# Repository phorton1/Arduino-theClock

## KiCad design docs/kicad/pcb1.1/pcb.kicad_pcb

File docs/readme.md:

# theClock - my first attempts at making a electromagnetic wooden geared clock

Please see [**theClock3**](https://github.com/phorton1/Arduino-theClock3)
for a more functional, and better documented electromagnetic wooden clock for **makers**.

This project is being documented *posthumously* in order to preserve the lineage of my clock oriented projects
so it **does contain all the fusion360 files, DXF files, and other results of the project** in case you are
interested.

## When and Why?

Around November of 2022, I had completed the [**20 mm CNC machine**](https://github.com/phorton1/Arduino-esp32_cnc20mm)
project and was using that machine to create various wooden boxes and other projects.  I was having fun with
the laser cutting capabilities of the machine and decided I wanted to try something with wooden gears in it.
After a few weeks of mulling the kinds of things I could build with wooden gears ... novelty boxes, or maybe
wooden robots, cars, etc ... I hit on the notion of making a **wooden clock**.

So I began obsessing about clocks in general and wooden clocks in particular.  One prolific online source
of information is [**Brian Law**](https://www.woodenclocks.co.uk/) and his many clocks, webpages and designs.
Although not wooden, I quickly found [**Steve Peterson's**](https://www.youtube.com/@stevesclocks)
series of 3D printed clocks interesting.  I explored dozens of existing designs, from the most artistic,
to the most rudimentary simple escapement mechanisms.

My diode laser cutter is limited to cutting about 1/4" (or less) wood.

As it turned out, I could not find a single existing design that I could make using
the tools and materials I had available to me.  My goal was to **laser cut** most of the pieces
from thin, cheap, available plywood and possibly 3D print a few other parts.   This is not
to dis any of the many great, and complete, and sometimes free designs out there.  But, I
actually live in an apartment, don't have access to a table saw or similar typical woodworking
tools.  Most of the designs for clocks that I found online involved thicker woods, typically hardwoods,
and the use of the usual woodworking tools.

Although you can find a number of *clock
making kits* that use laser cut plywood **for sale** online, I could not find any free
online designs for such clocks.  Finally, with regards to the existing laser pre-cut
kits that *are* available, even for pay, none of them captured what I was trying to achieve.
Although beautiful and complex, the available *kits* are more or less uniformly intended as
snap-together novelty clocks and not really designed to be permanently constructed and
act as actual time pieces.

So, I determined I would just learn what was necessary and design my clock from scratch.

Probably the first requirement that I arrived at was that I wanted the clock to be
electromagnetically driven. The real study and discipline of
[**Horology**](https://en.wikipedia.org/wiki/History_of_timekeeping_devices),
and clocks as we know them, centrally involves the evolution of
[**gravity escapement mechanisms**](https://en.wikipedia.org/wiki/Escapement#Deadbeat_escapement).
But I did not want to build a clock that had to be rewound (or it's weight lifted) every day or week.
I wanted something I could put on a shelf, and forget, and that would keep time fairly
reliably ... that is that it would function as an actual clock in my living space.

So I elected early to have an electromagnetically driven pendulum, while maintaining
the idea that it would have wooden, laser cut gears.

I thought it would be *so much easier* than it turned out to be!  In fact, my original
notion was to build a **chaotic clock** that, despite being chaotic, still kept accurate time, an idea I
may yet revisit.  The idea was to build a dual pendulum clock that could be intentionally
driven into a chaotic motion, but that could be recovered to periodicity at
small amplitudes, and then to have the clock randomly intersperse chaotic movements
of the pendulum with regular time-keeping movements to correct and adjust for
the chaos.  It was to be called **The Perception of Time**, alluding to the fact
that humans just do not experience time in a linear manner. Also, in my dreams,
it would be artistic and/or have crazy gear trains like squares, triangles, or helices.

In any case, that remains a project for the possible future as I decided that,
since I only wanted to spend a few weeks on the project, I had just better build
a simple clock.

**I had a lot to learn**

## A Few Requirements

As with all of my projects, I started off by listing a few requirements for the project.

- It would largely be made of **thin laser cut plywood** (as described above)
- It would use an **electromagnetically driven pendulum**
- It would have concentric **hour**, **minute**, and **second hands**
- It would keep **reasonably accurate** time, the definition of which was yet to be determined.
- It would **not** look like, or be constructed like a **snap together kit**.
- It would look like a **permanent construction** .. a *real clock*, yet ....
- It would be built in such a way that it could be **disassembled** and **repaired** or **modified** if necessary
- It would make use of an **MPU** (Microprocessor) like an Arduino or an ESP32
- It would have a custom made **PCB** (Printed Circuit Board)
- The PCB and electromagnetic coils would be hidden, unobtrusively powering the clock
- The **magnet** on the pendulum would **pass between two coils** rather than *over one coil* (discussed below)

The requirement about being able to be **disassembled** and and **repaired** or **modified** warrants
a brief discussion.

Especially since I had no idea if the clock would even work, or what refinements might be needed,
I decided to design the clock in such a way that, as much as practicable, I would be able to disassemble
and re-assemble it multiple times in case I needed to modify the mechanical aspects of the clock
along the way.   Also, not having any idea about the lifespan of
such a clock, it was important to me to be able to, at some point in the future, disassemble and
repair and/or rebuild the clock in case the gears or parts of the wooden mechanism
*wear out*.

Given a general idea of the requirements of the project, I then proceeded into a **research
phase** to learn as much as possible about these kinds of clocks before constructing one.
I downloaded and analyzed virtually any clock design that I could find, even if they did not
match my construction criteria, just to get an idea of how other people had approached
building wooden (or any) clocks.  This included a number of complete **Fusion 360** designs,
but also a number of available (free) online **books** about the subject.

## Electromagnetism and Gravity

It was a wonderful journey!   I spent days, and sometimes all night, reading histories
and perspectives of clock making, which turn out to be pretty fundamental to science,
and the development of civilization as we know it.  The **research phase** broadened
out into a review, as it were, of pretty much **the entire history of science** lol.

It led me to re-touch my basic understandings of **physics** and **mathematics**,
going back through **Newton** and *Calculus 101*, but really took me on a journey
through most of human history.   From sun dials, to the Aztecs and their calendars,
Pythagoras and the Greeks, I was all over the place reading about the history of how humans
came up with the notion of time ... and measuring it.

Galileo famously notices the period of a [**pendulum**](https://en.wikipedia.org/wiki/Pendulum)
is nearly independent of it's amplitude ... that is that a pendulum swings at about
the same rate regardless of how wide it swings.
[Christiaan Huygens](https://en.wikipedia.org/wiki/Christiaan_Huygens) creates
a gravity escapement mechanism to produce the world's most accurate clock
of the 1600's ... accurate to a few minutes a day.

One of my favorite reads was learning more about
[Robert Hooke](https://en.wikipedia.org/wiki/Robert_Hooke), the
creation of the [Royal Society](https://en.wikipedia.org/wiki/Royal_Society),
and Hooke's rivalry with Issac Newton.  **Did you know that Robert
Hook was the first human to ever create a tone of a known frequency?**
LOL, he created a gear mechanism with a paper card, and by knowing
the gear ratios and counting off the seconds with a clock, he could
ascertain the frequency of the resulting tone.

It was approximately a G# lol, on his piano, in case you're wondering,
although the **tuning fork** would not be invented for another 150 years,
and the semi world-wide standardardization to A440 tuning until the
middle 1900's - after WW1.

In any case, or rather, of course, that led me through the whole
[Age of Enlightment](https://en.wikipedia.org/wiki/Age_of_Enlightenment)
before I could relish re-learning about the greats in the discovery
and understanding of [Electromagnetism](https://en.wikipedia.org/wiki/Electromagnetism).
Volta!  Gauss!  Ampere!  Lorenz!  Michael effing Faraday!

**And then came [Maxwell](https://en.wikipedia.org/wiki/James_Clerk_Maxwell)**

All of sudden we're talking about **the speed of light** !!!

Another fun fact: **Did you know that [Michelson](https://en.wikipedia.org/wiki/Albert_A._Michelson)
and [Morely](https://en.wikipedia.org/wiki/Edward_W._Morley) used a *pendulum* in their
groundbreaking attempts to measure the speed of light?** Yup.  They used one to determine
the local gravity in Pasadena, CA, which was part of their calculations of the speed of
light.

In any case, all of this stuff was very interesting, and I got to re-learn
a lot, and learn a lot of new stuff as I started designing silly wooden clocks!

## Experiments - Pendulum Prototypes

I thought it would be a good idea to just build a pendulum and see if I
could get it to swing with an electromagnet.   I 3D printed a little
white pendulum that was about 5 inches high and using some coils removed
from a couple of of micro-solenoids I had laying around. I
created a circuit with an Arduino and a motor controller module
to send pulses of electricity to the coils.

That worked in a few hours.  The pendulum had a magnet in it, and
could be made to swing back and forth (fairly rapidly).

Then I designed and built a bigger pendulum, learning in the process that
I'm not so bright!   LOL.

I thought I would make a [**linear motor**](https://en.wikipedia.org/wiki/Linear_motor)
(I was still clinging to the *chaotic pendulum* idea),
so that I could swing the pendulum really fast, or really slow,
or even stop it in the middle of a swing.   Since magnets
are cheap, and coils are expensive (and fairly hard to make), and since
most linear motors **move the coil** through stationary magnetic fields,
that was my initial stab.

I designed the Pendulum in Fusion 360.  I salvaged the magnet wire
from the transformer of an old wall wart and hand wound the coils.  I laser cut
the pendulum from wood and 3D printed the plastic framework to go on some
2020 aluminum extrusions.
I put **two coils** on the pendulum and had it swing through the fields of a
series of magnets, and extended the bread boarded **Arduino** control circuit,
thinking I could then simply control it's position
in real time as one would with a linear motor.

**Nope**.

I got it moving, but it turns out that (a) the pendulum wants to swing at a particular rate;
it did not want to move at arbitrary frequencies,
(b) you basically don't want a bunch of wires and junk on the pendulum,
as that decreases it's accuracy, and, perhaps more importantly,
in my configuration (c) the electromagnetic coils were not nearly strong
enough to stop and hold the pendulum at any given point, (d) this linear
motor was at best, like a stepper motor, and the motion was jerky and
not smooth.

Before moving on, I removed the magnets, one at a time, in a series of experiments,
until I ended up with a single magnet and the two coils on the pendulum that
I could sort of control.  At that point, though I could get the pendulum to swing
fairly reliably, I could not really control it's period.

Another thing I *did* experiment with here was using the Arduino to not only
**pulse the electromagnet** to attract or repulse the magnets
and move the pendulum, but was also to **use the coil as a
sensing device**.   Since a coil moving through a magnetic field
creates a current, I could measure that current with the
computer and tell, for example, when the coil passed a magnet.

Most single coil electromagnetic clocks use that current sensing
capability (and a simple circuit) to detect a zero crossing for
the timing for delivering the repulsive impulse to keep the pendulum
moving.

After a few days I decided to just go ahead and start designing the
gears and things for a wooden clock.

## First (Bad) Design

Designing the gears and mechanics in Fusion 360 was not difficult, but
was time consuming.

Somehow I landed on the notion that my clock would have
four coils (two about the center of the swing and two at
the extremes) -- which are really eight coils since, in
my design, the magnet moves **between** the coils.

*Another side note:  I could find absolutely **no scientific studies**
or analyses about the effect of a magnet moving **between** two coils.
There were plenty of scholarly articles on solenoids, coils,
magnets moving near a coil, etc, but nowhere could I find an analysis
of the math involved when a magnet passes **between** two coils.*

I wanted my magnet to pass **between** two coils, rather than **over**
a single coil, as most magnetic clocks do, because I felt that the
**vector of force** from a coil underneath a magnet would tend
to make the pendulum **bump** as the impulse is applied.  The
force would not be **orthogonal** to the pendulum's axis of rotation.
By having the magnet move between the two coils, the majority of
the force would be put into moving the pendulum along it's line
of travel, rather than *up* or *down* (assuming the pulse is
applied shortly after the *zero crossing*) and that seemed
**more efficient** to me.

I was also *not thrilled* with the technique of **using the
coils as sensors**.   I did experiment with it extensively,
and it works, but it is onerous in the circuit and code to change the
Arduino's pins from **input** to **output** to be able sense milliamp
currents one millisecond, and then deliver 1/2 amp or more to the same coil
a few milliseconds later and the results were not that great.

Because I knew I would want to **know where the pendulum was** in it's
swing (particularly zero crossing), and I did not like the *coil sensing*
approach, in this initial design, because I had a few on hand,
I also added [**five hall sensors**](https://en.wikipedia.org/wiki/Hall_effect_sensor),
which are electrical components that can tell when a magnet is near
them, bracketting the four (pairs) coils with the idea that
I could use the information, particularly the zero crossing, but
also the extent of the swings, in controlling the clock..

Mind you, I still don't have any idea if, or how this thing is gonna work.

But in building the test rig above, I finally determined that I needed **some kind
of an actual full clock** to even test these concepts.  The **friction**
from the gears and the work that needs to be done, the **ratchet** mechanism,
the **length and weight of the pendulum**, all play a role in how fast
the clock ticks and how much force is needed to move the pendulum.

So I just designed and built a damned clock lol, pressing through the
design even if I was not sure about if, or how, it would work.

An actual full implementation allowed me to test the simple mechanics,
gears, gear ratios, the ratchet mechanism, and so on, all of which worked
**pretty good**, more or less, on the fist build, right out of the
design gate, as it were.

I also made a [**coil winding machine**](https://github.com/phorton1/Arduino-CoilWindingMachine), as hand winding
these coils is really tedious and inexact, and I had to
make eight of them!!

I started off using an **Arduino** on a breadboard as the computer, but
quickly decided that I would rather have a more powerful and sophisticated **ESP32**, not
only because it's speed would allow me a lot more flexibility in the
implementation, but also because the ESP32 **includes WiFi and a built in RTC**
(real time clock), whereas the Arduino doesn't.  The RTC
would come into play to keep the clock accurate, and with the WiFi I would
be able to access **NTP** (Network Time Protocol) as well as provide a **WebUI** for
remote **control, monitoring, and debugging** of the clock.

So I also designed a circuit for an ESP32 and built the first custom PCB
for the clock.  With 4 (pairs of) coils, sigh, I used **two L293D** H-bridge
motor drivers so that I could control each (pair of) coils to either
repulse or attract the pendulum magnet under MPU control.

I got it going ... it ticked and tocked .. and the second
hand moved, but the clock was not even close to keeping good time

I called this version 1.0.

## Simplifying and Getting it working (sort of)

Without going into too much gruesome detail, I quickly learned that
having so many coils was a headache and did not really help me to
control the pendulum and it's timing.  What I needed was a single,
bigger, and more powerful coil, so I retrofitted the clock with
a single bigger coil.

I also ended up *embedding the coils in epoxy* so that I could eliminate
the plastic (on the *bobbin*) between the coil and the magnet to
reduce the distance and increase the force.  Even 1mm of distance
less increased the force applied to the pendulum significantly.

### Adding the magnetic spring

As I said, I thought it would be easier.  With my 4 coil design I had
been planning to control the frequency of the pendulum by using the
outer pair of coils to either attract, or more likely repulse, the
pendulum on each swing so that I could speed it up or slow it down.

That also proved difficult to impossible, in practice, for me to accomplish.

I hit on the idea of controlling the frequency **BY** controlling
the amplitude at about that time.    **If I just had a spring ...**

hmmm ... what if I just have **one coil** and put a set of permanent
magnets near the extreme of the swing that repulse the magnet in the pendulum?
Then wouldn't it be the case that on wide swings the pendulum would **bounce**
off those springs, making it go faster?   And then couldn't I reduce the
amplitude of the pendulum (by putting less energy into it) so that it would
not bounce off the springs, and would then tick slower as a result of that?

So I retrofitted the clock with these **magnetic spring** thingees,
switched to a single coil, rewrote most of the software, and within
a week or so of the first build, I had achieved a clock
that could sort of keep time.

I called this **version 1.1**.

## Version 2

I spent a lot of time messing around version 1.1, particularly
mucking around with the code.

It was not pretty.  There is a PID controller
that adjusted the energy put into each swing based on the
milliseconds error, but I also needed to add a few "heuristics" (**kludges**)
to keep the clock running reasonably ... to prevent it
from "stalling" while trying to slow down, or banging back and
forth while trying to speed up.

After a week of effort, Version 1.1 was probably accurate to a few minutes a day.

Since I wanted to make a clock as a gift to someone for Christmas, and I was
running out of time, I did one more quick design pass to rectify the worst
problems with Clock1 and pressed on with another build:

- the wooden frame was not square and the clock did not sit flat,
  so I designed a 3D printed base which at least kept the clock
  itself from rocking back and forth
- I formalized the design of the magnetic springs so that they
  could be more accurately adjusted.
- I designed and built a **new PCB** that only used one LM293D
  motor controller
- I added a **face** with numbers to the clock.

I laser cut a whole new clock, and all the parts, 3d printed stuff,
made the new circuit board, soldered it up, wound coils, sanded all the gears (pain!),
painted everything, and so on, put it together, and, after putting
it through a quick testing cycle, I sent it away.

I would say that it was accurate to a few minutes a day at it's best.

I did not even get a chance to test it for a week before gifting it :-(

Nor had I, in the code, gotten around to any notion of utilizing
the ESP32's RTC (real time clock), much less using NTP (Network
Time Protocol) to make the clock accurate over any time scales
(though I had laid the groundwork in the code, WebUI, etc)

It just tried to beat at 1000ms per swing.

I called this "theClock - Version 2"

## Design problems with Versions 1 & 2

Part of it was the mechanics .. it was missing beats or sometimes
grabbing two gears.  There were friction problems, and, I think,
misalignment causing the gears to bind at times. But also
part of it was the software and heuristics, which
were hamstrung with the *information* available to the software in
order to control the pendulum, and somewhat hastily written
and not really that well tested.

From these initial clocks I came up with the following list of **problems**:

- The use of **dowels** to connect the different **planes** of the clock did not work well.   If the dowels
  were fitted into thick pieces of hardwood, and the holes were drilled square, then the dowels could
  facilitate a **square frame**.  However, because the holes are merely in thin pieces of plywood,
  the dowels were not inherently square to the frame.  In other words, there were alignment issues
  between the *planes* of the clock, which caused **a lot of friction** and **binding of the clock**
  as the hands and gears turned.    This was particularly true when taken with the requirement that the
  clock be **disassemble-able** and the clock was only **screwed** together in the final assembly.
  To get it to work, I had to *dry build** the clock, twist the dowels and position the planes
  the best I could, **apply epoxy glue**, and then literally hold it together with my hands as the glue set
  in order to achieve any degree of alignment.
- The **ratchet mechanism** requires the pendulum to do **all of it's work** while swinging in one
  direction, and does **no work** while swinging in the other direction.  This made the pendulum
  swing (and forces involved) **lopsided** and caused an uneven beating of the clock. It would
  swing much more, and more easily, to one side than to the other.
- More importantly, the **ratchet mechanism** is directly coupled the pendulum to the pawls, so
  that **the wider the pendulum swings, the further the second hand moves**!!  This resulted
  in the mechanism being unreliable, particularly to the degree that I was trying to control
  the **frequency** of the pendulum by increasing or decreasing the **amplitude** of the swing.
  I found that, at wide swings, the pawl would sometimes **grab two teeth** and advance the clock
  **two seconds** at a time, or arguably worse, in smaller swings it would sometimes **fail to move
  the seconds hand at all** (a condition I called a **stall**).
- The five **Hall Sensors** did not provide me with enough **resolution** about the position
  of the pendulum to implement a good **PID Controller** (algorithm for controlling the clock),
  and as a result, the swing would vary wildly while trying to speed up or slow down the clock,
  sometimes banging the left and right limits of travel (and grabbing two teeth!) or other times
  failing to even grab a tooth and move the seconds hand (stalling).
- Due to time constraints I had not been able to implement any code that took advantage
  of the ESP32 **RTC** (Real Time Clock) or the available **NTP** (Network Time Protocol) to
  make the clock more accurate.

Although I compensated for the resolution problem by putting heuristics into the code for these cases,
in subsequent clocks I utilized a different, more accurate way of sensing the position of the pendulum
which led to a much simpler algorithm, and smoother and more precise control of the
pendulum, in turn resulting in a much more pleasing and consistent swing.

### Postscript

After I built [**theClock3**](https://github.com/phorton1/Arduino-theClock3), I felt bad
for my old forlorn clock version 1 sitting there on the shelf, so I retrofitted it with
the **AS5600 angle sensor** and **software** from *theClock3* resulting in it *keeping
much better time* and having a *much nicer swing* (even though it is not as accurate,
or trouble free as *theClock3*) ..

### **Next:** After versions 1 & 2, I designed and implemented [**theClock3**](https://github.com/phorton1/Arduino-theClock3)

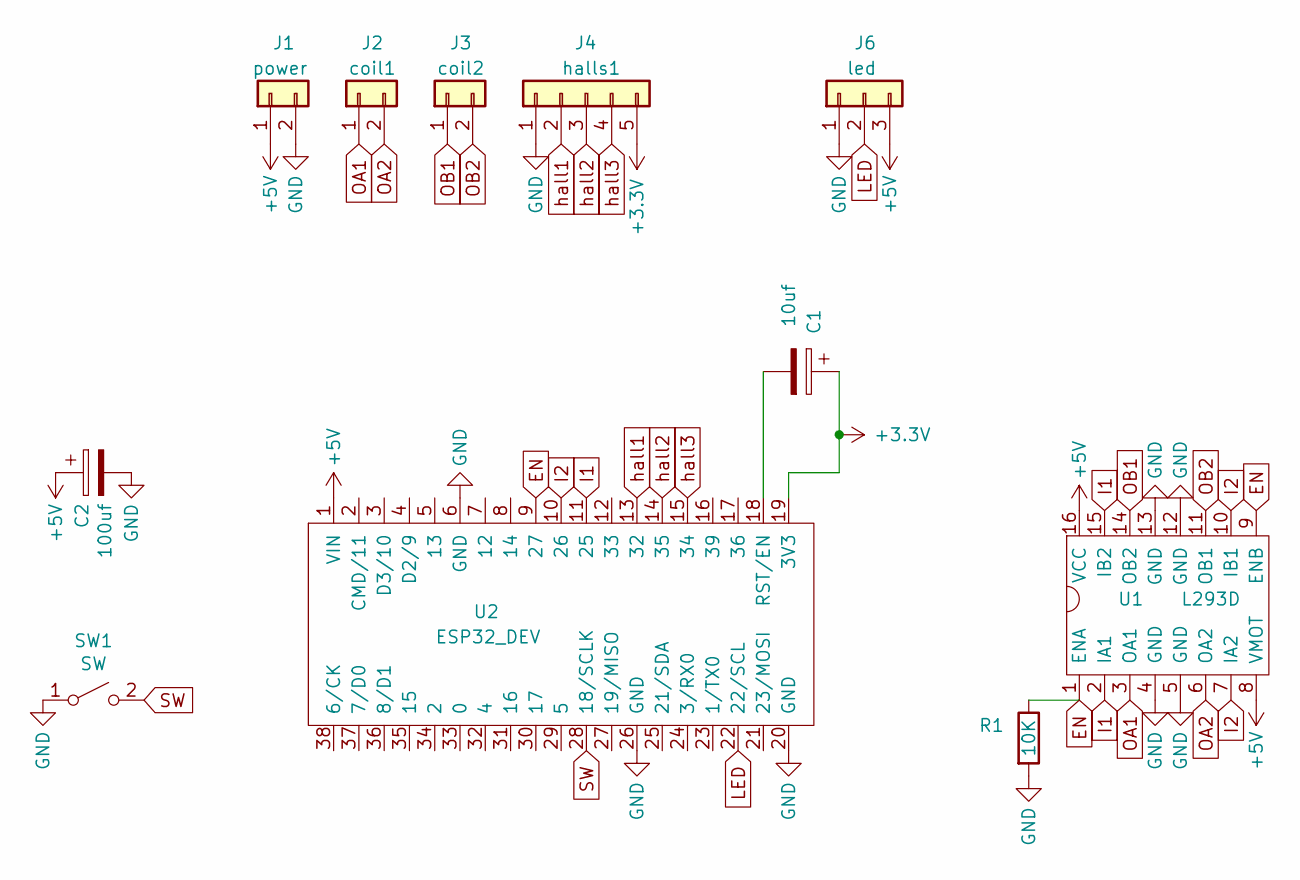
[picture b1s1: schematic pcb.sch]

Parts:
C1: 10uf; my2pin
C2: 100uf; my2pin
J1: power; my2pin
J2: coil1; my2pin
J3: coil2; my2pin
J4: halls1; my5Pin
J6: led; my3pin
R1: 10K; myResistor
SW1: SW; right_angle_button
U1: L293D; myDip16
U2: ESP32_DEV; ESP32-DEV

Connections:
+3V3: C1.1, J4.5, U2.19 (3V3)
+5V: C2.1, J1.1, J6.3, U1.8 (VMOT), U1.16 (VCC), U2.1 (VIN)
EN: R1.1, U1.1 (ENA), U1.9 (ENB), U2.9 (27)
GND: C2.2, J1.2, J4.1, J6.1, R1.2, SW1.1 (A), U1.4 (GND), U1.5 (GND), U1.12 (GND), U1.13 (GND), U2.6 (GND), U2.20 (GND), U2.26 (GND)
I1: U1.2 (IA1), U1.15 (IB2), U2.11 (25)
I2: U1.7 (IA2), U1.10 (IB1), U2.10 (26)
LED: J6.2, U2.22 (22/SCL)
unnamed: C1.2, U2.18 (RST/EN)
OA1: J2.1, U1.3 (OA1)
OA2: J2.2, U1.6 (OA2)
OB1: J3.1, U1.14 (OB2)
OB2: J3.2, U1.11 (OB1)
SW: SW1.2 (B), U2.28 (18/SCLK)
hall1: J4.2, U2.13 (32)
hall2: J4.3, U2.14 (35)
hall3: J4.4, U2.15 (34)

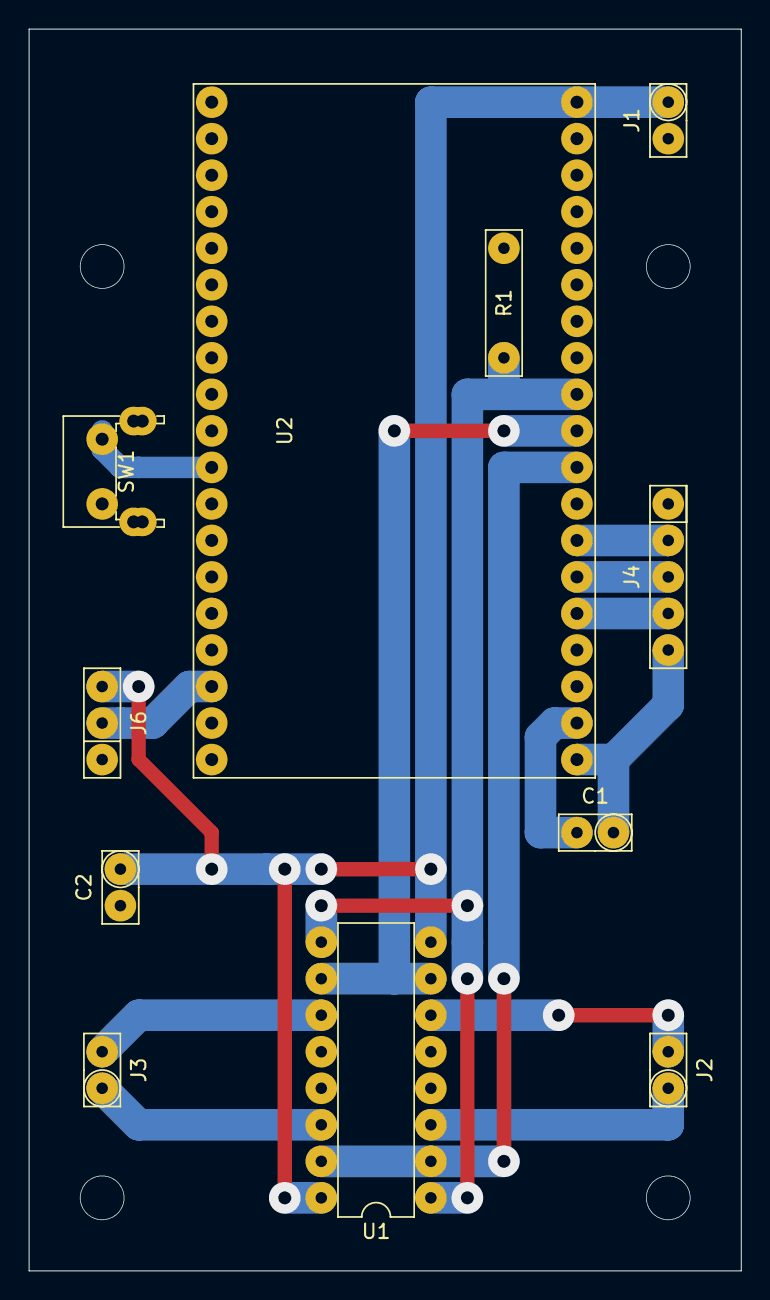
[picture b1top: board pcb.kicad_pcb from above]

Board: 2 copper layers, 49.5 x 86.4 mm, 11 parts (0 on the bottom side), 16 nets.

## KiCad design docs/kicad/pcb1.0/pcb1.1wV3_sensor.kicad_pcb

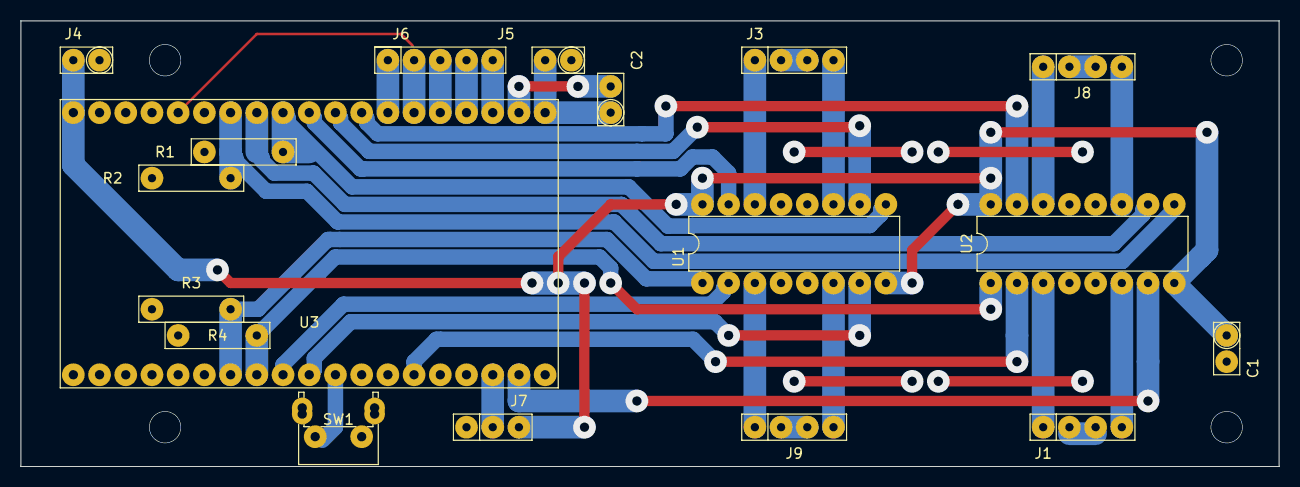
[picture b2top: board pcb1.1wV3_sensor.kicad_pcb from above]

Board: 2 copper layers, 121.9 x 43.2 mm, 18 parts (0 on the bottom side), 35 nets.

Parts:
C1: 100uf; my2pin
C2: 10uf; my2pin
J1: coil48; my4pin
J3: coil15; my4pin
J4: power; my2pin
J5: hall_power; my2pin
J6: halls; my5Pin
J7: led; my3pin
J8: coil126; my4pin
J9: coil37; my4pin
R1, R2, R3, R4: 10K; myResistor
SW1: SW; right_angle_button
U1, U2: L293D; myDip16
U3: ESP32_DEV; ESP32-DEV

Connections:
+3V3: C2.1, J5.2, U3.19
+5V: C1.1, J4.2, J7.3, U1.8, U1.16, U2.8, U2.16, U3.1
ENA: R1.1, U1.9, U3.9
ENB: R2.1, U2.9, U3.7
ENC: R3.1, U1.1, U3.32
END: R4.1, U2.1, U3.31
GND: C1.2, J4.1, J5.1, J7.1, R1.2, R2.2, R3.2, R4.2, SW1.1, U1.4, U1.5, U1.12, U1.13, U2.4, U2.5, U2.12, U2.13, U3.6, U3.20, U3.26
IA1: U1.10, U3.11
IA2: U1.15, U3.10
IB1: U2.10, U3.8
IB2: U2.15, U3.12
IC1: U1.2, U3.30
IC2: U1.7, U3.29
ID1: U2.2, U3.25
ID2: U2.7, U3.21
LED: J7.2, U3.22
unnamed: C2.2, U3.18
unnamed: J1.2, J1.3
unnamed: J3.2, J3.3
unnamed: J8.2, J8.3
unnamed: J9.2, J9.3
OA1: J3.4, U1.11
OA2: J3.1, U1.14
OB1: J8.4, U2.11
OB2: J8.1, U2.14
OC1: J9.1, U1.3
OC2: J9.4, U1.6
OD1: J1.1, U2.3
OD2: J1.4, U2.6
SW: SW1.2, U3.28
hall1: J6.1, U3.13
hall2: J6.2, U3.14
hall3: J6.3, U3.15
hall4: J6.4, U3.16
hall5: J6.5, U3.17

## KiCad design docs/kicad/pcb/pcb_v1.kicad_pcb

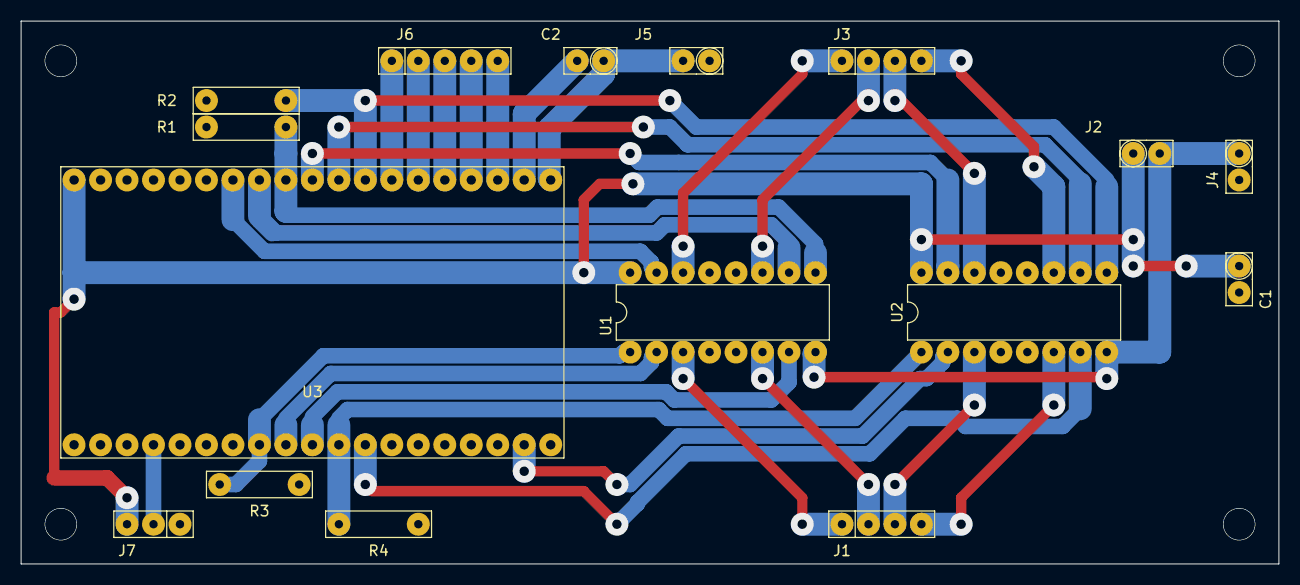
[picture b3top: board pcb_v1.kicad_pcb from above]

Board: 2 copper layers, 120.7 x 52.1 mm, 16 parts (0 on the bottom side), 31 nets.

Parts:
C1: 100uf; my2pin
C2: 10uf; my2pin
J1: coil34; my4pin
J2: jumper; my2pin
J3: coil12; my4pin
J4: power; my2pin
J5: hall_power; my2pin
J6: halls; my5Pin
J7: led; my3pin
R1, R2, R3, R4: 10K; myResistor
U1, U2: L293D; myDip16
U3: ESP32_DEV; ESP32-DEV

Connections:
+3V3: C2.1, J5.2, U3.19
+5V: C1.1, J2.1, J7.3, U1.16, U2.16, U3.1
ENA: R1.1, U1.9, U3.9
ENB: R2.1, U2.9, U3.12
ENC: R3.1, U1.1, U3.31
END: R4.1, U2.1, U3.28
GND: C1.2, J4.2, J5.1, J7.1, R1.2, R2.2, R3.2, R4.2, U1.4, U1.5, U1.12, U1.13, U2.4, U2.5, U2.12, U2.13, U3.6, U3.20, U3.26
IA1: U1.10, U3.8
IA2: U1.15, U3.7
IB1: U2.10, U3.11
IB2: U2.15, U3.10
IC1: U1.2, U3.30
IC2: U1.7, U3.29
ID1: U2.2, U3.21
ID2: U2.7, U3.27
LED: J7.2, U3.35
unnamed: C2.2, U3.18
OA1: J3.2, U1.11
OA2: J3.1, U1.14
OB1: J3.4, U2.11
OB2: J3.3, U2.14
OC1: J1.1, U1.3
OC2: J1.2, U1.6
OD1: J1.3, U2.3
OD2: J1.4, U2.6
VSS: J2.2, J4.1, U1.8, U2.8
hall1: J6.1, U3.13
hall2: J6.2, U3.14
hall3: J6.3, U3.15
hall4: J6.4, U3.16
hall5: J6.5, U3.17

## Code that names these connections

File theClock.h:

#pragma once

#include <Arduino.h>
#include <myIOTDevice.h>

#define COMPILE_VERSION  2
	// sets the (old) static HALL calibration values for V1 vs V2
	// and the myIOT device name and version

#define PIN_HALL1	32
#define PIN_HALL2	35
#define PIN_HALL3	34

// Note that ENB, INB1, and INB2 are sent out for backward
// compatability for V1 circuit board but unused on V2

#define PIN_ENA		27
#define PIN_INA1	25
#define PIN_INA2	26
#define PIN_ENB		4
#define PIN_INB1	17
#define PIN_INB2	5

#define PIN_LEDS	22
#define PIN_BUTTON  18

#define PIXEL_MAIN		0
#define NUM_PIXELS		1

#define MY_LED_BLACK    0x000000
#define MY_LED_RED      0x440000
#define MY_LED_GREEN    0x003300
#define MY_LED_BLUE     0x000044
#define MY_LED_CYAN     0x003333
#define MY_LED_YELLOW   0x333300
#define MY_LED_MAGENTA  0x330033

#define MY_LED_WHITE    0x444444

#define MY_LED_ORANGE   0x402200
#define MY_LED_REDMAG   0x400022
#define MY_LED_BLUECYAN 0x002240


//------------------------
// theClock definition
//------------------------

#define ID_RUNNING			"RUNNING"
#define ID_PID_MODE			"PID_MODE"
#define ID_PLOT_VALUES		"PLOT_VALUES"

#define ID_HALL_THRESH		"HALL_THRESH"

#define ID_POWER_LOW      	"POWER_LOW"
#define ID_POWER_HIGH      	"POWER_HIGH"
#define ID_POWER_MAX      	"POWER_MAX"
#define ID_POWER_START      "POWER_START"

#define ID_DUR_LEFT      	"DUR_LEFT"
#define ID_DUR_RIGHT      	"DUR_RIGHT"
#define ID_DUR_START		"DUR_START"

#define ID_PID_P			"PID_P"
#define ID_PID_I			"PID_I"
#define ID_PID_D			"PID_D"

#define ID_CLEAR_STATS		"CLEAR_STATS"

#define ID_CUR_TIME			"CUR_TIME"
#define ID_TIME_LAST_START  "LAST_START"
#define ID_STAT_RUNTIME		"TIME_RUNNING"
#define ID_STAT_BEATS		"BEATS"
#define ID_STAT_RESTARTS	"RESTARTS"
#define ID_STAT_STALLS_L	"STALLS_LEFT"
#define ID_STAT_STALLS_R	"STALLS_RIGHT"
#define ID_STAT_ERROR_L		"ERROR_LOW"
#define ID_STAT_ERROR_H		"ERROR_HIGH"
#define ID_STAT_DUR_L		"DUR_LOW"
#define ID_STAT_DUR_H		"DUR_HIGH"
#define ID_MIN_POWER_USED	"MIN_POWER_USED"
#define ID_MAX_POWER_USED	"MAX_POWER_USED"

#define ID_STAT_INTERVAL	"STAT_INTERVAL"



class theClock : public myIOTDevice
{
public:

    theClock();
    ~theClock() {}

    virtual void setup() override;
	virtual void loop() override;

private:

    static const valDescriptor m_clock_values[];

	static bool _clock_running;
	static bool _pid_mode;
	static uint32_t _plot_values;

	static int _hall_thresh;

	static int _power_low;		// STATIC: power when sensor reached; PID: mininum power
	static int _power_high;		// STATIC: power when sensor not reached;  PID: starting power
	static int _power_max;      // PID: maximum power
	static int _power_start;    // power during startup pulse

	static int _dur_left;		// duration of left power pulse for both PID and STATIC
	static int _dur_right;		// duration of right power pulse for both PID and STATIC
	static int _dur_start;		// duration of startup pulse

	static float _pid_P;
	static float _pid_I;
	static float _pid_D;

    static uint32_t _time_last_start;
	static uint32_t _cur_time;
	static String _stat_time_running;
	static uint32_t _stat_beats;
	static uint32_t _stat_restarts;
	static uint32_t _stat_stalls_left;
	static uint32_t _stat_stalls_right;
	static int _stat_error_low;
	static int _stat_error_high;
	static int _stat_dur_low;
	static int _stat_dur_high;
	static uint32_t _min_power_used;
	static uint32_t _max_power_used;

	static uint32_t _stat_interval;

	static void startClock();
	static void stopClock();
	static void clearStats();

    static void onClockRunningChanged(const myIOTValue *desc, bool val);
    static void onPIDModeChanged(const myIOTValue *desc, bool val);

	static void run();
	static void clockTask(void *param);
};


extern theClock *the_clock;

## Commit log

2022-11-27 added design.md (to test github directory structure)
2022-11-30 prep for V2 (single coil) circuit board by duplicating and moving kicad stuff into separate folders
2022-12-02 updated to V1.1 - single coil and 3 hall sensors
2022-12-11 renamed pcb 2.0 to 1.1 - WIP
2022-12-11 moved pcb1.1 mounting hole
2022-12-14 finished pcb
2022-12-18 CLOCK 2.0 - initial changes: version number, hall calibrations
2022-12-19 sanity checking before new algorithm
2022-12-20 MAJOR REV to V2 - Change to single right pulse algorithm, get rid of "over positions" add WIFI on/off (default==off) via base/bat/platform_setup.pm, cleanup all defines, etc, etc, etc
2022-12-20 implemented button control and led pixel feedback
2022-12-20 uploaded new software to old clock V1
2022-12-27 added dur_left to cope with my weak v1.1 clock; tuned
2022-12-29 Tuning old v1 clock
2023-01-04 added STAT_DURATION to configuration
2023-01-22 COMMENTS - brought comments up to date with my V1.0 running fairly well
2023-02-18 added some NTP test code
2023-04-19 diagram v1.3 (v1.1 plus v3 sensor & software)
2023-06-07 updated to new captive.html (Source Code is now Obsolete but will be retained to show pics of old clocks)
2023-06-12 initial commit of documentation WIP
2023-06-12 test commit and push
2023-06-13 upload initial PUBLIC version
2023-06-13 remove obsolete statement ... it is what it is
2023-06-13 readme typos
2023-06-16 added link to new Arduino-CoilWindingMachine repository
2023-10-10 added LICENSE.TXT and empty docs/readme.md to most public repositories
2023-10-20 updated to myIOT changes from a while ago - ID_DEVICE_WIFI changed to ID_WIFI - VALUE_STORE_MQTT_SUB - changed to VALUE_STORE_SUB
2024-02-20 normalize myIOT data directories against Arduino/Libraries myIOT/data master
2024-03-01 get rid of /data folder in prep for submodule
2024-03-01 made 'data' directory into submodule of myIOT/data_master
2024-07-18 submodule(data) auto_commit(3ef3db13) iotCommon.js - added app disable control functionality
2024-07-19 submodule(data) auto_commit(9478759f) addl iotCommon.js submodule changes for control and disabled_classses
2024-09-21 submodule(data) auto_commit(83767cf1) Added a Widget tab to the main myIOT webpage; added jqplot CSS and JS files; wrote iotPlot.js prototype of charting within a "widget" - see fridgeController chec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
2024-09-22 submodule(data) auto_commit(0465efe4) myIOT Widets II - introduce basic HTTP caching; refactor myIOT iotPlot.js into iotCommon.js, cleanup Widget concepts and code; sanity checkcin
2024-09-22 submodule(data) auto_commit(e76456cf) iotPlot.js - minor change to Fix Zooming; otherwise "comments only"
2024-09-24 submodule(data) auto_commit(86b02898) created a WS based Plotter!
2024-09-25 submodule(data) auto_commit(331f60b7) refined myIOT plotter with LEGENDS and using device specific PLOT_TYPES if available; theClock3 implementation of PLOT_CYCLES and PLOT_WAVES
2024-09-25 submodule(data) auto_commit(18ec6f60) iotPlot.js - missing ctx.lineWidth = 1; for plot itself
2024-09-26 submodule(data) auto_commit(68039dc2) prep for bilgeAlarm bar chart widget - reworked myIOTDataLog to send records from back of file until dt stamp is met, which required myIOTWebServer to use HTTP 1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
2024-09-29 submodule(data) auto_commit(416ed000) added prototype bilgeAlarm jqPlot Widget using added "alt_data_format" and custom chart_header and chart_data code in onCustomLink(). modified myIOT/data index.h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
2024-10-01 submodule(data) auto_commit(2407a228) added global DEGREE_TYPE and VALUE_STYLE_TEMPERATURE, supprted in webUI, dataLog, and Charts
2024-10-06 submodule(data) auto_commit(28556b88) iotCommon.js - changed keep_alive timings and const's to vars to allow debugging at runtime
2024-10-07 submodule(data) auto_commit(f3e2065d) reduce size of WS status fields in index.html
2024-10-10 submodule(data) auto_commit(b622c3ba) Use regular javascript alert instead of myAlert and hide progress on upload_error
2024-10-19 submodule(data) auto_commit(c0e7ba5a) add better resizing to iotChart.js
2024-10-21 submodule(data) auto_commit(b811e3f8) move generic uiButtons to myIOTButtons; implement initial tempController uiScreen and PCB board(s)
2024-10-25 submodule(data) auto_commit(fdbad871) fix myIOTServer with new chart stuff (pass uuids, caching, etc)
2025-12-15 submodule(data) auto_commit(b649fc3a) iotChart.js - added scheme for setting device specific series colors
2025-12-18 submodule(data) auto_commit(1adaeb45) reworked iotChart.js incremental update scheme starting with Arduino-boat-drainPump
2025-12-18 submodule(data) auto_commit(b6ac0c88) starting in Arduino-boat-arirco, major rework of iotChart.js and how charts are implemented - use common chart.html instead of specific/extra_data/device_chart.h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
2025-12-18 submodule(data) auto_commit(1efc7b72) rework iotChart.js::determineNumberTicks() starting with drain_pump
2025-12-18 submodule(data) auto_commit(78894e93) change onChartResize() to use create_chart() instead of built in jqplot.replot()
2025-12-18 submodule(data) auto_commit(40916b0c) separate iotChart.js doChart() as init only method from onXXX() UI methods - yet another rework of iotChart.js and myIOTDataLog starting with fridgeController
2025-12-18 submodule(data) auto_commit(b923e44d) back to static html for chart.html; got rid of myIOTDataLog::getChartHtml() starting with tempController
2025-12-18 submodule(data) auto_commit(a4e2ed81) change chart.html and iotChart.js to use and remove style "degree_hidden" for devices that chart things with degrees
2025-12-18 submodule(data) auto_commit(a9754dbc) fixed renamed control _degree_type
2025-12-18 submodule(data) auto_commit(03555741) fix malformed chart.html <select id='_chart_period'> text
2025-12-19 submodule(data) auto_commit(1cb3d61a) add onChartResize() back to chart.html
2025-12-19 submodule(data) auto_commit(253976a9) more changes to iotChart.js starting with tempController so at least refresh works *well* if no zooming involved
2025-12-19 commit parents
2025-12-20 submodule(data) auto_commit(eccd1fcc) iotChart.js - added save/restore of series visibility and refactored code
2025-12-31 submodule(data) auto_commit(2a8db875) add degree_type to myIOT chart_header for use in initializing iotChart.js
2026-02-22 submodule(data) auto_commit(37a6a76c) added framework for chart.html to pass "data_name" to allow multiple charts per device; ALSO store most recent chart period in browser storage
2026-03-04 submodule(data) auto_commit(75bcbcb5) iotChart.js - added smaller (UINT8, CENTIGRADE8, UINT8x10) iotDataLog LOG_TYPES and updated client ctors
2026-03-04 submodule(data) auto_commit(d6f02205) added myIotTempSensor "raw" accessors & used to shrink fridgeController.dataLog file size; got rid of FAKE_COMPRESSOR
2026-03-04 got rid of dubious ability to turn myIOT WIFI off and on
2026-03-05 submodule(data) auto_commit(ecc76888) update myIOT data submodule readme.md to remove forward references to actual implmented device repos
2026-03-07 submodule(data) auto_commit(5dbe3136) Save chart visibility and zorders in locsl storage
2026-04-04 submodule(data) auto_commit(a0279fca) New iotChart tooltips and dataLog record maintenance feature.
2026-04-04 submodule(data) auto_commit(de0689cf) disable Scan/Delete endpoints and just View data records for devices that have graphs, but no SD card
2026-06-28 submodule(data) auto_commit(eadab9ea) added myIOTDataLog type LOG_COL_TYPE_INT16_10 to support volts (fridgeController)
